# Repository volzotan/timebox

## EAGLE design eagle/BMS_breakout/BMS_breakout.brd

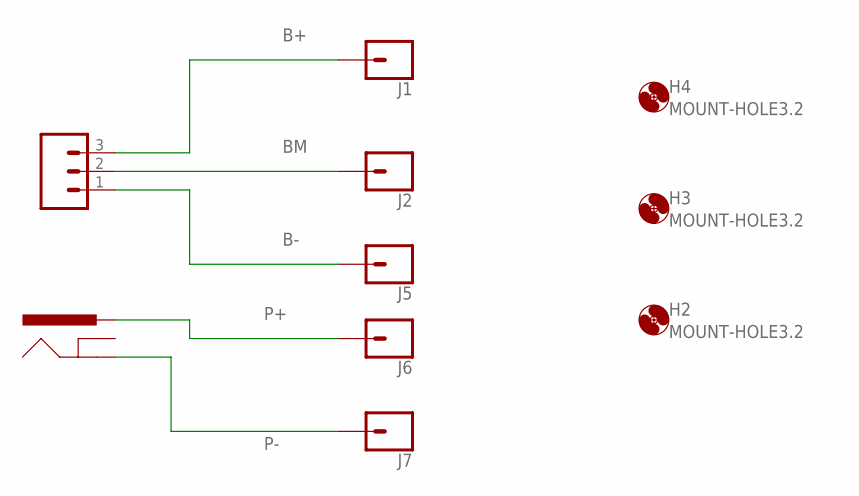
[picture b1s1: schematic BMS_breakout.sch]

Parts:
H2, H3, H4: MOUNT-HOLE3.2; 3,2
J1, J2, J5, J6, J7: CONN_01; 1X01
J3: CONN_03-SCREW-5MM; SCREWTERMINAL-5MM-3
J4: POWER_JACKPTH_BREAD; POWER_JACK_PTH_BREAD

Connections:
B+: J1.1, J3.3
B-: J3.1, J5.1
BM: J2.1, J3.2
P+: J4.PWR, J6.1
P-: J4.GND, J7.1

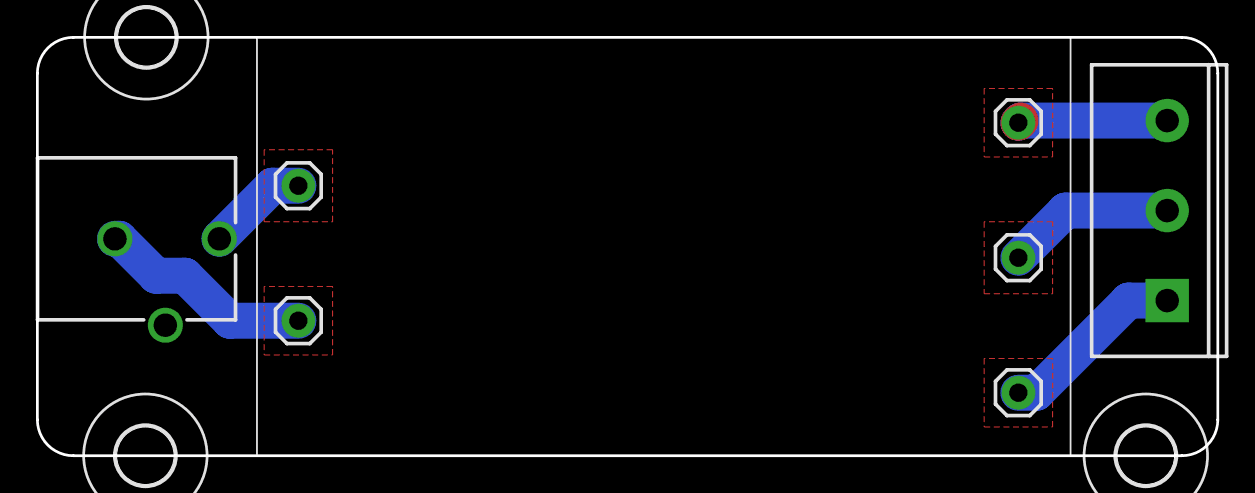
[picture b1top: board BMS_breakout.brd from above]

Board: 2 copper layers, 65.6 x 23.2 mm, 10 parts (0 on the bottom side), 5 nets.

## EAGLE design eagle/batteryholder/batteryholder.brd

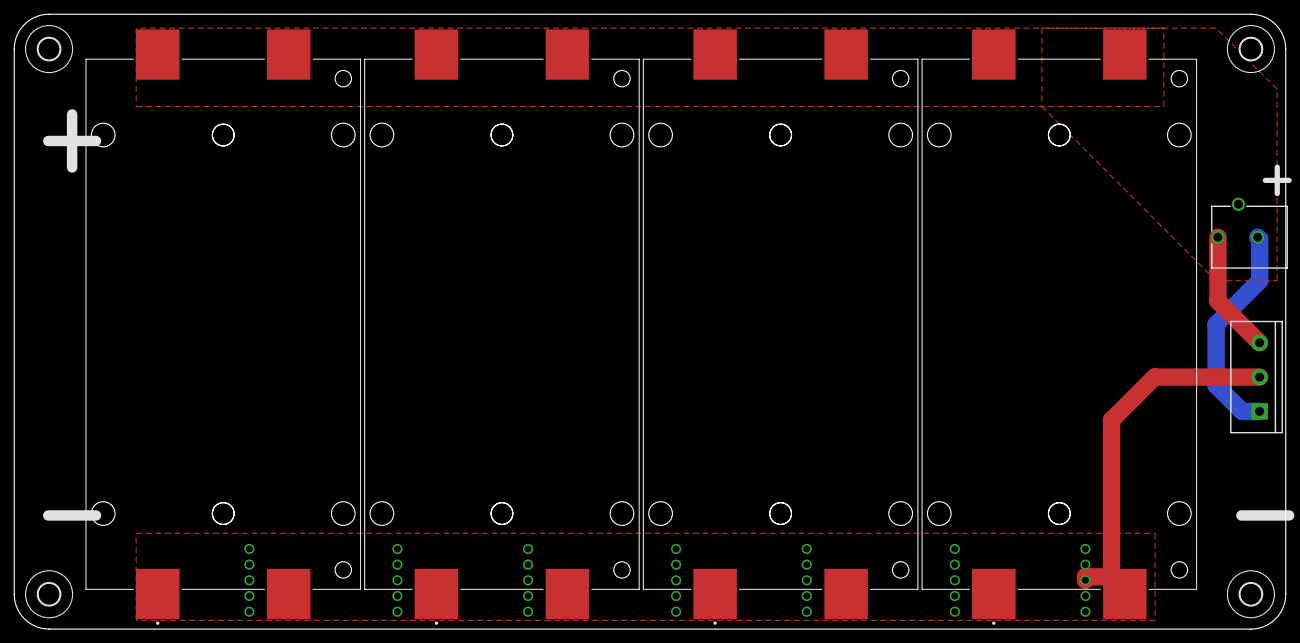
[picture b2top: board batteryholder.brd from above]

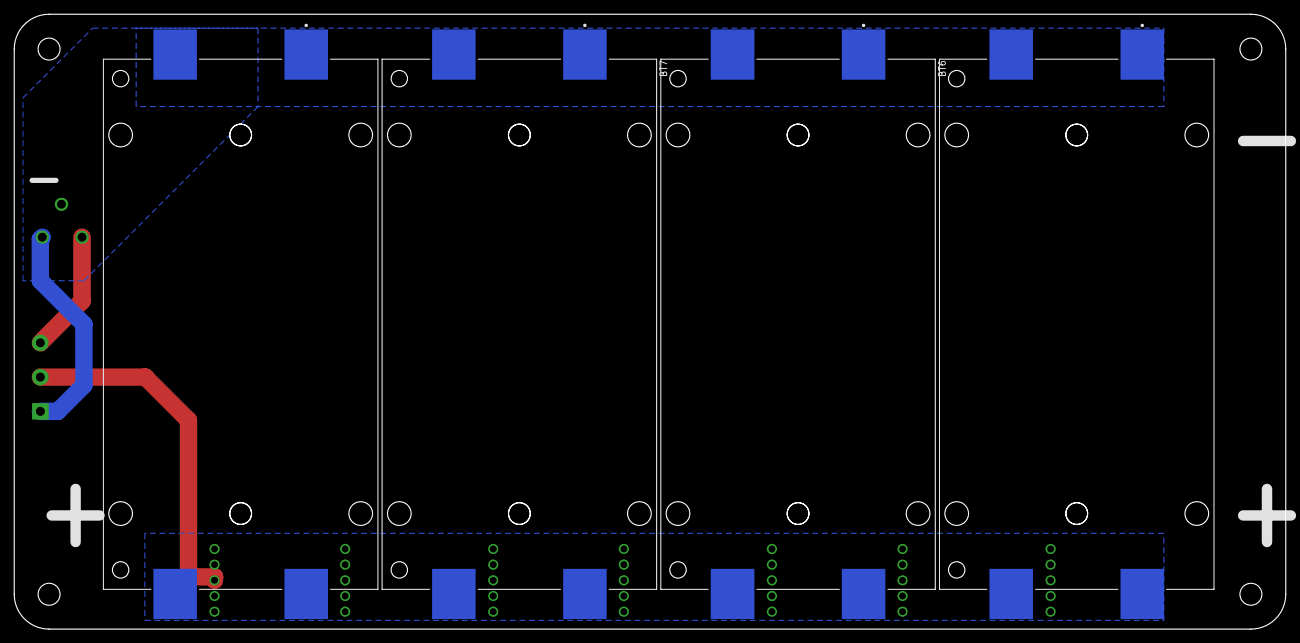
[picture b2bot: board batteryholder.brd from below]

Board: 2 copper layers, 185.4 x 89.7 mm, 14 parts (4 on the bottom side), 3 nets.

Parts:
BT1, BT2, BT3, BT4, BT5, BT6, BT7, BT8: KEYSTONE_1048KEYSTONE_1048_0_0; KEYSTONE_1048_0
H1, H2, H3, H4: MOUNT-HOLE3.2; 3,2
J1: SCREWTERMINAL-5MM-3
J3: POWER_JACKPTH_BREAD; POWER_JACK_PTH_BREAD

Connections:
BOTTOM_MINUS: BT5.1, BT5.3, BT6.1, BT6.3, BT7.1, BT7.3, BT8.1, BT8.3, J1.1, J3.GND
TOP_MINUS: BT1.1, BT1.3, BT2.1, BT2.3, BT3.1, BT3.3, BT4.1, BT4.3, BT5.2, BT5.4, BT6.2, BT6.4, BT7.2, BT7.4, BT8.2, BT8.4, J1.2
TOP_PLUS: BT1.2, BT1.4, BT2.2, BT2.4, BT3.2, BT3.4, BT4.2, BT4.4, J1.3, J3.PWR

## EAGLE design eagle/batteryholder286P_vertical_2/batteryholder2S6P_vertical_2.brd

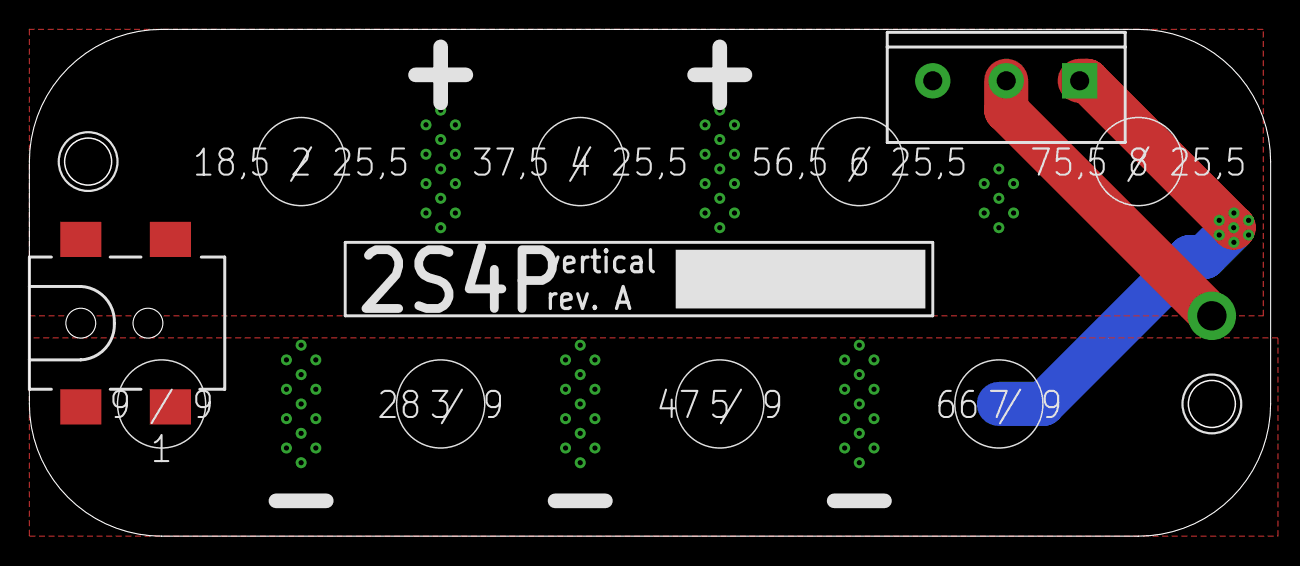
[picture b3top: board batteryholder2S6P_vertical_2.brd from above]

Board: 2 copper layers, 84.5 x 34.5 mm, 3 parts (0 on the bottom side), 3 nets.

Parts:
J1: 1X01_2MM
J2: 5.5x2.1mm Barrel; POWER_JACK_SMD
J3: SCREWTERMINAL-5MM-3

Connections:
B+: J2.VIN0, J3.3
B-: J2.GND, J2.P$4, J3.1
unnamed: J1.1, J3.2

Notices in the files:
parts and their libraries:
SparkFun-Connectors: Licensing: Creative Commons ShareAlike 4.0 International - https://creativecommons.org/licenses/by-sa/4.0
